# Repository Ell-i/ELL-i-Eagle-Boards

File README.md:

ELL-i Eagle Boards
==================

ELL-i Printed Circuit Boards in Eagle CAD format.

This repository contains both completed designs and designs that are
still work in progress.  The designs are licensed under Creative
Commons Attribution Share-Alike licence; for more information, see

  http://www.ell-i.org/Licensing

The designs (other than Ellduino) use components from the ELL-i and
SparkFun Eagle Libraries.  If you want to base your design on the
ELL-i designs, it is a good idea to install the ELL-i and SparkFun
Eagle Libraries; for more information, see

  https://github.com/Ell-i/ELL-i-Eagle-Libraries

Furthermore, you want to include the libraries into your library path,
as explained in README.md there.

Each of the directories in this repository forms a separate
(Eagle project)[https://learn.sparkfun.com/tutorials/using-eagle-schematic/create-a-project],
with its own (``eagle.epf`` file)[http://www.cadsoftusa.com/training/faq/#5].
The ``eagle.epf`` files stored in the repository have been carefully
hand-crafted, in order not to include any information about the active
windows, libraries, or the Eagle platform.

Modifying the project settings
------------------------------

By default, the Eagle projects in this repository have been stored
with auto-save off; that is, the ``eagle.epf`` file contains the
``AutoSaveProject=0`` directive.  Consequently, whenever you work on
the project, by default the window sizes and positions, etc, are not
saved.  If you *do* decide to save the settings (see below), you
*should* tell git to
(ignore local changes)[http://juststuffreally.blogspot.fi/2008/10/if-you-have-file-that-lives-in-git.html]
to ``eagle.epf``.

If you want to save the project settings, you can do that manually.
To do so, go to the *Control Panel* window in Eagle, and then select
``File->Save all`` from the menu.  This saves information about the
Eagle platform and Windows to the ``eagle.epf`` file.

After that, git will tell you that the ``eagle.epf`` file has been
changed and should be committed.  To tell git to ignore the local
changes, give the following command in the project directory:
```
git update-index --assume-unchanged build.properties
```
After that, git (ignores uncommitted
changes)[https://www.kernel.org/pub/software/scm/git/docs/git-update-index.html]
to the ``eagle.epf`` file.

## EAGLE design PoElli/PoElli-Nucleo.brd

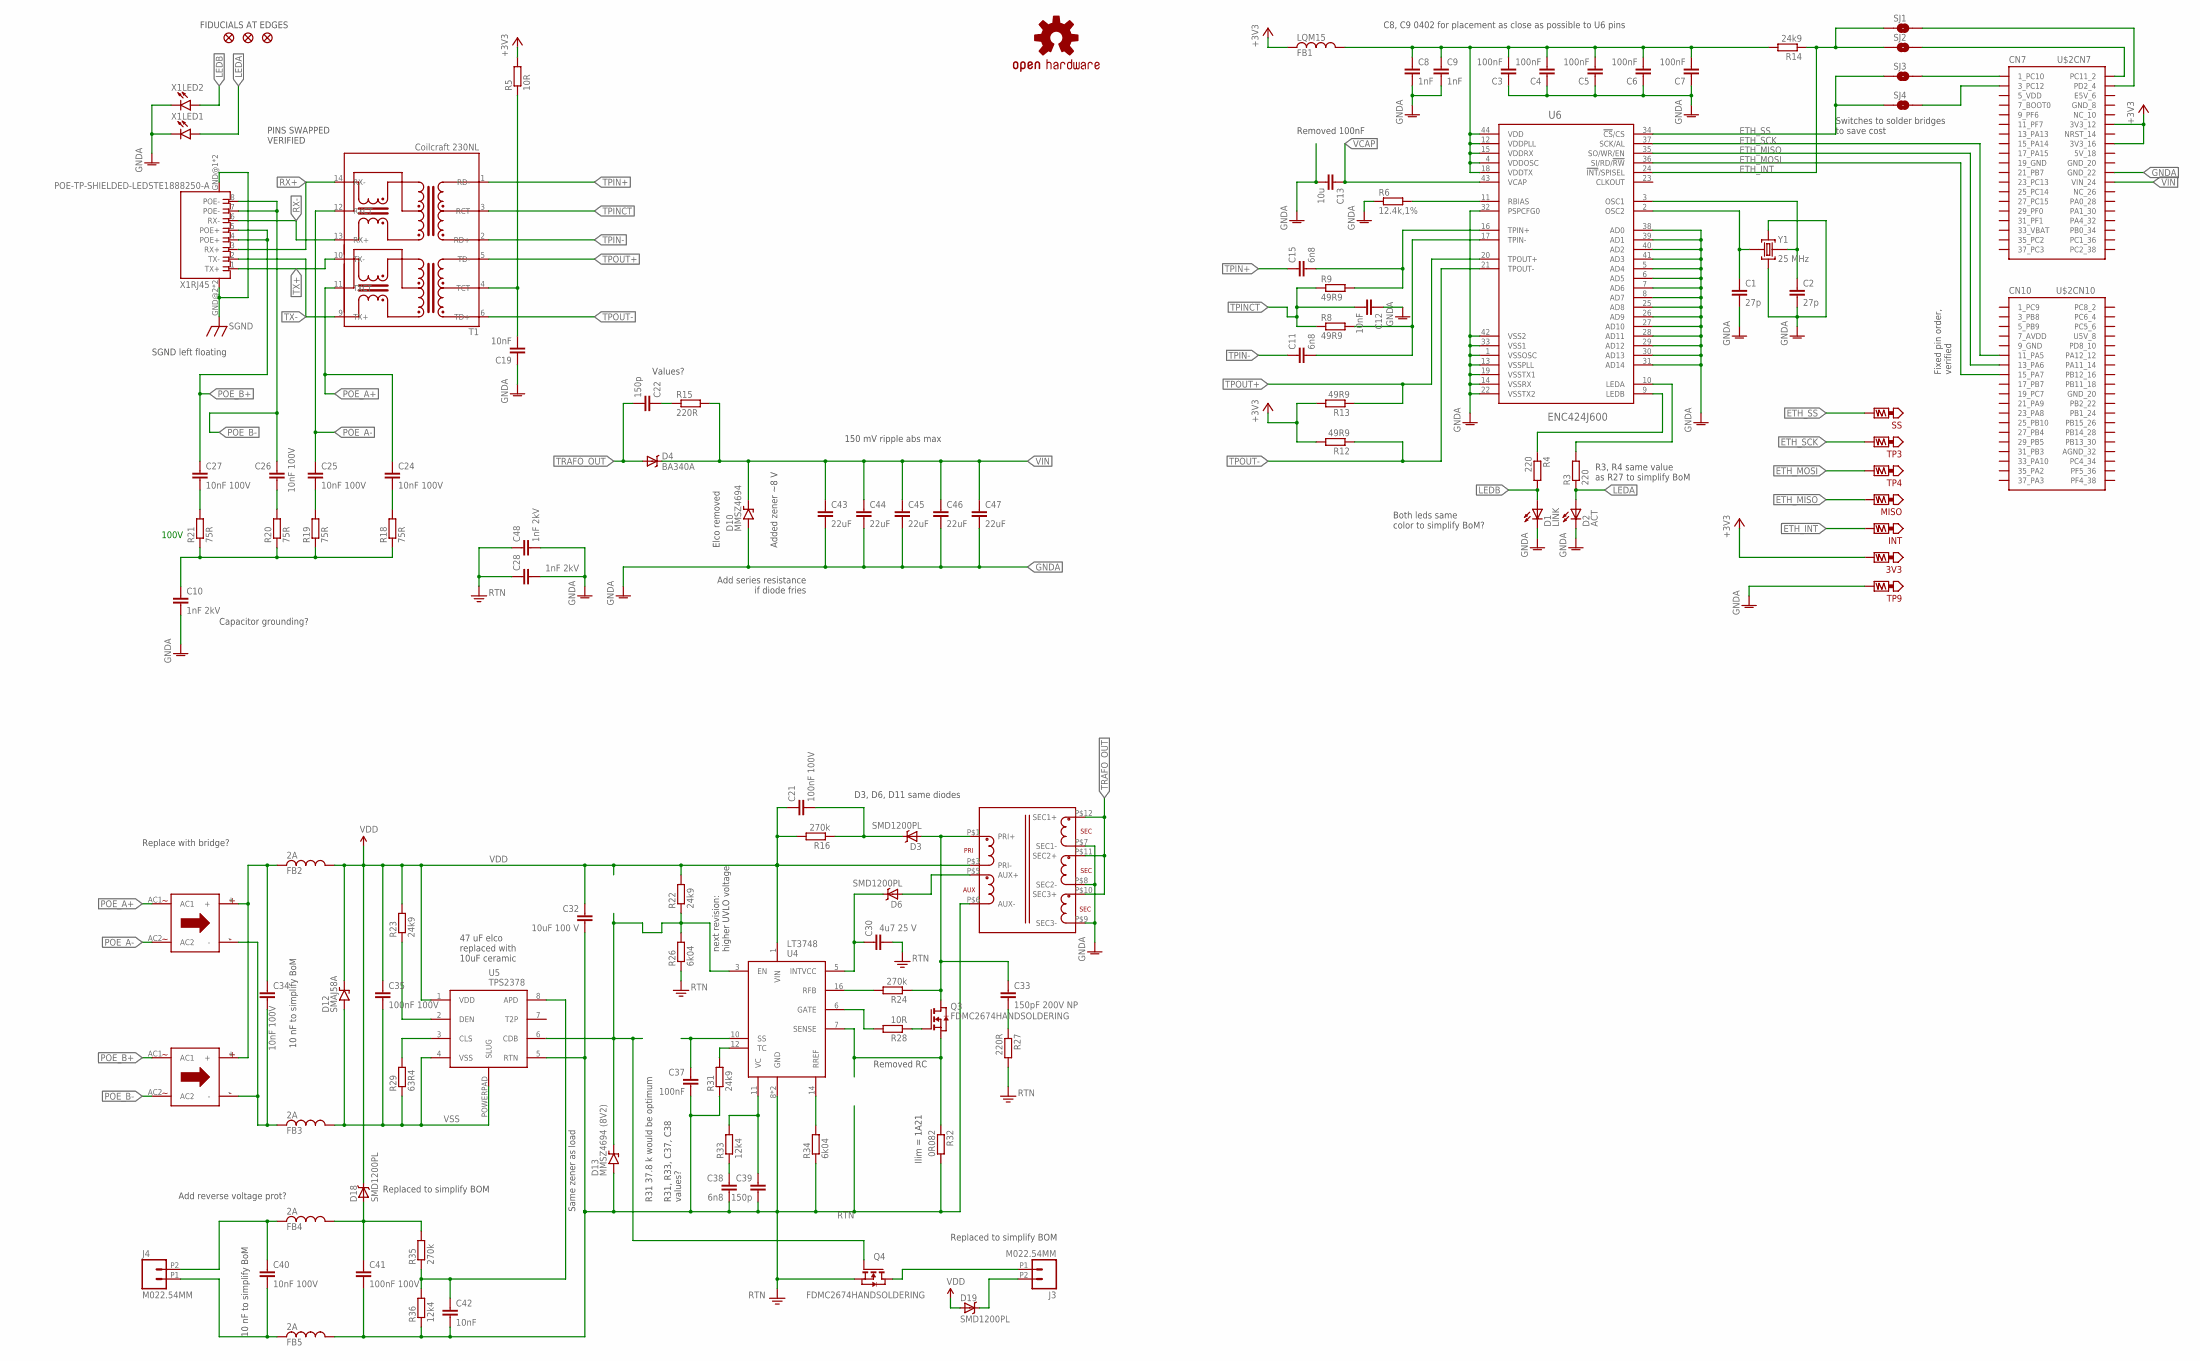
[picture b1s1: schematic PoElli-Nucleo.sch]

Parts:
3V3: 3V3; TP_5000
B1, B2: BRIDGE-RECTIFIER; MBS1
C1, C2: 27p; SMD0603-B
C3, C4, C5, C6, C7, C37: 100nF; SMD0603-B
C8, C9: 1nF; SMD0402-B
C10, C28, C48: 1nF 2kV; SMD1206-A
C11, C15, C38: 6n8; SMD0603-B
C12, C19, C42: 10nF; SMD0603-B
C13: 10u; SMD0603-B
C21, C35, C41: 100nF 100V; SMD0603-B
C22, C39: 150p; SMD0603-B
C24, C25, C26, C27, C34, C40: 10nF 100V; SMD0603-B
C30: 4u7 25 V; SMD0603-B
C32: 10uF 100 V; SMD2220-REFLOW
C33: 150pF 200V NP; SMD0603-B
C43, C44, C45, C46, C47: 22uF; SMD1206-A
D1: LINK; LED-0603
D2: ACT; LED-0603
D3, D6, D18, D19: SMD1200PL; SOD-123FL-A
D4: BA340A; SMA-DIODE
D10: MMSZ4694; SOD-123FL-A
D12: SMAJ58A; SMA
D13: MMSZ4694 (8V2); SOD-123FL-A
FB1: LQM15; SMD0603-A
FB2, FB3, FB4, FB5: 2A; SMD0603-A
FID1, FID2, FID3: FIDUCIAL1X2; FIDUCIAL-1X2
INT: TEST_POINT-5000; TP_5000
J3, J4: M022.54MM; 1X02_2.54_SCREWTERM
LOGO1: OSHW-LOGOM; OSHW-LOGO-M
MISO: MISO; TP_5021
Q3, Q4: FDMC2674HANDSOLDERING; MLP8L33_HS
R3, R4: 220; SMD0603-A
R5, R28: 10R; SMD0603-B
R6: 12.4k,1%; SMD0603-B
R8, R9, R12, R13: 49R9; SMD0603-B
R14: 24k9; SMD0603-A
R15, R27: 220R; SMD0603-B
R16: 270k; SMD0603-A
R18, R19, R20, R21: 75R; SMD0603-B
R22, R23, R31: 24k9; SMD0603-B
R24, R35: 270k; SMD0603-B
R26, R34: 6k04; SMD0603-B
R29: 63R4; SMD0603-B
R32: 0R082; SMD0603-B
R33, R36: 12k4; SMD0603-B
SJ1, SJ3: SOLDERJUMPERNC2; SJ_2S-NOTRACE
SJ2, SJ4: SOLDERJUMPERNO; SJ_2S-NO
SS: SS; TP_5021
T1: Coilcraft 230NL; COILCRAFT-ETH1-230L
T2: FLYBACK-3_OUTPUTS_749119350; WE_749119350
TP3: SCK; TP_5021
TP4: MOSI; TP_5021
TP9: GND; TP_5000
U4: LT3748; MSOP16(12)
U5: TPS2378; SO08-POWERPAD
U6: ENC424J600; TQFP44-0.8MM
U$2: NUCLEO-SHIELD-20PIN; NUCLEO-SHIELD-UNDERSIDE-SHORT-20-PINHEADER
X1: POE-TP-SHIELDED-LEDSTE1888250-A; TE1888250-A
Y1: 25 MHz; CRYSTAL-SMD-3225-GND

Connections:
+3V3: 3V3.P$1, FB1.P$1 (1), R5.P$2 (2), R12.P$2 (2), R13.P$2 (2), U$2.CN7_12 (3V3_12), U$2.CN7_16 (3V3_16)
ENC-3V3: C3.P$2 (2), C4.P$2 (2), C5.P$2 (2), C6.P$2 (2), C7.P$2 (2), C8.1, C9.1, FB1.P$2 (2), R14.P$2 (2), U6.4 (VDDOSC), U6.12 (VDDPLL), U6.15 (VDDRX), U6.18 (VDDTX), U6.44 (VDD)
ETH_INT: INT.P$1, R14.P$1 (1), SJ1.1, SJ2.1, U6.24 (!INT!/SPISEL)
ETH_MISO: MISO.P$1, U6.35 (SO/WR/EN), U$2.CN10_13 (13_PA6)
ETH_MOSI: TP4.P$1, U6.36 (SI/RD/!RW), U$2.CN10_15 (15_PA7)
ETH_SCK: TP3.P$1, U6.37 (SCK/AL), U$2.CN10_11 (11_PA5)
ETH_SS: SJ3.1, SJ4.1, SS.P$1, U6.34 (!CS!/CS)
GNDA: C1.P$2 (2), C2.P$2 (2), C3.P$1 (1), C4.P$1 (1), C5.P$1 (1), C6.P$1 (1), C7.P$1 (1), C8.2, C9.2, C10.P$2 (2), C12.P$1 (1), C13.P$2 (2), C19.P$1 (1), C28.P$2 (2), C43.P$2 (2), C44.P$2 (2), C45.P$2 (2), C46.P$2 (2), C47.P$2 (2), C48.P$2 (2), D1.C, D2.C, D10.A, R6.P$1 (1), T2.P$7 (SEC1-), T2.P$8 (SEC2-), T2.P$9 (SEC3-), TP9.P$1, U6.1 (VSSOSC), U6.5 (AD4), U6.6 (AD5), U6.7 (AD6), U6.8 (AD7), U6.13 (VSSPLL), U6.14 (VSSRX), U6.19 (VSSTX1), U6.22 (VSSTX2), U6.25 (AD8), U6.26 (AD9), U6.27 (AD10), U6.28 (AD11), U6.29 (AD12), U6.30 (AD13), U6.31 (AD14), U6.32 (PSPCFG0), U6.33 (VSS1), U6.38 (AD0), U6.39 (AD1), U6.40 (AD2), U6.41 (AD3), U6.42 (VSS2), U$2.CN7_22 (GND_22), X1.9 (C), X1.12 (C), Y1.2 (GND), Y1.4 (GND)
INTVCC: C30.P$1 (1), D6.C, U4.5 (INTVCC)
LEDA: D2.A, R3.P$1 (1), X1.10 (A)
LEDB: D1.A, R4.P$2 (2), X1.11 (A)
unnamed: J3.P1 (1), Q4.5 (D), Q4.6 (D), Q4.7 (D), Q4.8 (D), Q4.F1 (D)
unnamed: D19.C, J3.P2 (2)
unnamed: C10.P$1 (1), R18.P$1 (1), R19.P$1 (1), R20.P$1 (1), R21.P$1 (1)
unnamed: B1.+, B2.+, C34.P$1 (1), FB2.P$1 (1)
unnamed: R31.P$2 (2), U4.12 (TC)
unnamed: B1.-, B2.-, C34.P$2 (2), FB3.P$1 (1)
unnamed: SJ3.2, U$2.CN7_1 (1_PC10)
unnamed: SJ4.2, U$2.CN7_3 (3_PC12)
unnamed: SJ2.2, U$2.CN7_2 (PC11_2)
unnamed: SJ1.2, U$2.CN7_4 (PD2_4)
unnamed: C33.P$2 (2), R27.P$1 (1)
unnamed: C22.P$1 (1), R15.P$1 (1)
unnamed: R23.P$1 (1), U5.2 (DEN)
unnamed: R29.P$2 (2), U5.3 (CLS)
unnamed: C39.P$1 (1), R33.P$2 (2), U4.11 (VC)
unnamed: C38.P$1 (1), R33.P$1 (1)
unnamed: R28.P$2 (2), U4.6 (GATE)
unnamed: Q3.4 (G), R28.P$1 (1)
unnamed: Q3.1 (S), Q3.2 (S), Q3.3 (S), R32.P$1 (1), U4.7 (SENSE)
unnamed: C33.P$1 (1), D3.A, Q3.5 (D), Q3.6 (D), Q3.7 (D), Q3.8 (D), Q3.F1 (D), R24.P$1 (1), T2.P$1 (PRI+)
unnamed: D6.A, T2.P$5 (AUX+)
unnamed: R24.P$2 (2), U4.16 (RFB)
unnamed: R34.P$2 (2), U4.14 (RREF)
unnamed: C21.P$2 (2), D3.C, R16.P$1 (1)
unnamed: C1.P$1 (1), U6.2 (OSC2), Y1.1 (C1)
unnamed: C11.P$2 (2), R8.P$2 (2), U6.17 (TPIN-)
unnamed: C19.P$2 (2), R5.P$1 (1), T1.4 (TCT)
unnamed: R4.P$1 (1), U6.9 (LEDB)
unnamed: R3.P$2 (2), U6.10 (LEDA)
unnamed: R6.P$2 (2), U6.11 (RBIAS)
unnamed: C2.P$1 (1), U6.3 (OSC1), Y1.3 (C2)
unnamed: C27.P$2 (2), R21.P$2 (2)
unnamed: C24.P$2 (2), R18.P$2 (2)
unnamed: C25.P$2 (2), R19.P$2 (2)
unnamed: C26.P$2 (2), R20.P$2 (2)
unnamed: C40.P$1 (1), FB4.P$1 (1), J4.P2 (2)
unnamed: C42.P$1 (1), R35.P$1 (1), R36.P$2 (2), U5.8 (APD)
unnamed: C40.P$2 (2), FB5.P$1 (1), J4.P1 (1)
unnamed: C15.P$2 (2), R9.P$2 (2), U6.16 (TPIN+)
unnamed: C41.P$1 (1), D18.A, FB4.P$2 (2), R35.P$2 (2)
POE_A+: B1.AC1, C24.P$1 (1), T1.11 (TXCT)
POE_A-: B1.AC2, C25.P$1 (1), T1.12 (RXCT)
POE_B+: B2.AC1, C27.P$1 (1), X1.4 (POE+), X1.5 (POE+)
POE_B-: B2.AC2, C26.P$1 (1), X1.7 (POE-), X1.8 (POE-)
RTN: C28.P$1 (1), C30.P$2 (2), C32.P$2 (2), C37.P$2 (2), C38.P$2 (2), C39.P$2 (2), C41.P$2 (2), C42.P$2 (2), C48.P$1 (1), D13.A, FB5.P$2 (2), Q4.1 (S), Q4.2 (S), Q4.3 (S), R26.P$1 (1), R27.P$2 (2), R31.P$1 (1), R32.P$2 (2), R34.P$1 (1), R36.P$1 (1), T2.P$6 (AUX-), U4.8 (GND), U4.9 (GND), U5.5 (RTN)
RX+: T1.14 (RX-), X1.3 (RX+)
RX-: T1.13 (RX+), X1.6 (RX-)
SGND: X1.GND@1 (GND), X1.GND@2 (GND), X1.GND@3 (GND), X1.GND@4 (GND)
TPIN+: C15.P$1 (1), T1.1 (RD-)
TPIN-: C11.P$1 (1), T1.2 (RD+)
TPINCT: C12.P$2 (2), R8.P$1 (1), R9.P$1 (1), T1.3 (RCT)
TPOUT+: R13.P$1 (1), T1.5 (TD-), U6.20 (TPOUT+)
TPOUT-: R12.P$1 (1), T1.6 (TD+), U6.21 (TPOUT-)
TRAFO_OUT: C22.P$2 (2), D4.A, T2.P$10 (SEC3+), T2.P$11 (SEC2+), T2.P$12 (SEC1+)
TX+: T1.10 (TX-), X1.1 (TX+)
TX-: T1.9 (TX+), X1.2 (TX-)
U4_EN: D13.C, Q4.4 (G), R22.P$1 (1), R26.P$2 (2), U4.3 (EN), U5.6 (CDB)
U4_SS: C37.P$1 (1), U4.10 (SS)
VCAP: C13.P$1 (1), U6.43 (VCAP)
VDD: C21.P$1 (1), C32.P$1 (1), C35.P$1 (1), D12.C, D18.C, D19.A, FB2.P$2 (2), R16.P$2 (2), R22.P$2 (2), R23.P$2 (2), T2.P$3 (PRI-), U4.1 (VIN), U5.1 (VDD)
VIN: C43.P$1 (1), C44.P$1 (1), C45.P$1 (1), C46.P$1 (1), C47.P$1 (1), D4.C, D10.C, R15.P$2 (2), U$2.CN7_24 (VIN_24)
VSS: C35.P$2 (2), D12.A, FB3.P$2 (2), R29.P$1 (1), U5.4 (VSS), U5.POWERPAD (SLUG)

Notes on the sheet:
100V
Replace with bridge?
10 nF to simplify BoM
Add reverse voltage prot?
Both leds same color to simplify BoM?
R3, R4 same value as R27 to simplify BoM
R31, R33, C37, C38 values?
C8, C9 0402 for placement as close as possible to U6 pins
Values?
Removed 100nF
Switches to solder bridges to save cost
Elco removed
Added zener ~8 V
D3, D6, D11 same diodes
47 uF elco replaced with 10uF ceramic
Same zener as load
SGND left floating
150 mV ripple abs max
PINS SWAPPED VERIFIED
Capacitor grounding?
Removed RC
Ilim = 1A21
Fixed pin order, verified
Replaced to simplify BOM
FIDUCIALS AT EDGES
Add series resistance if diode fries
next revision: higher UVLO voltage
R31 37.8 k would be optimum

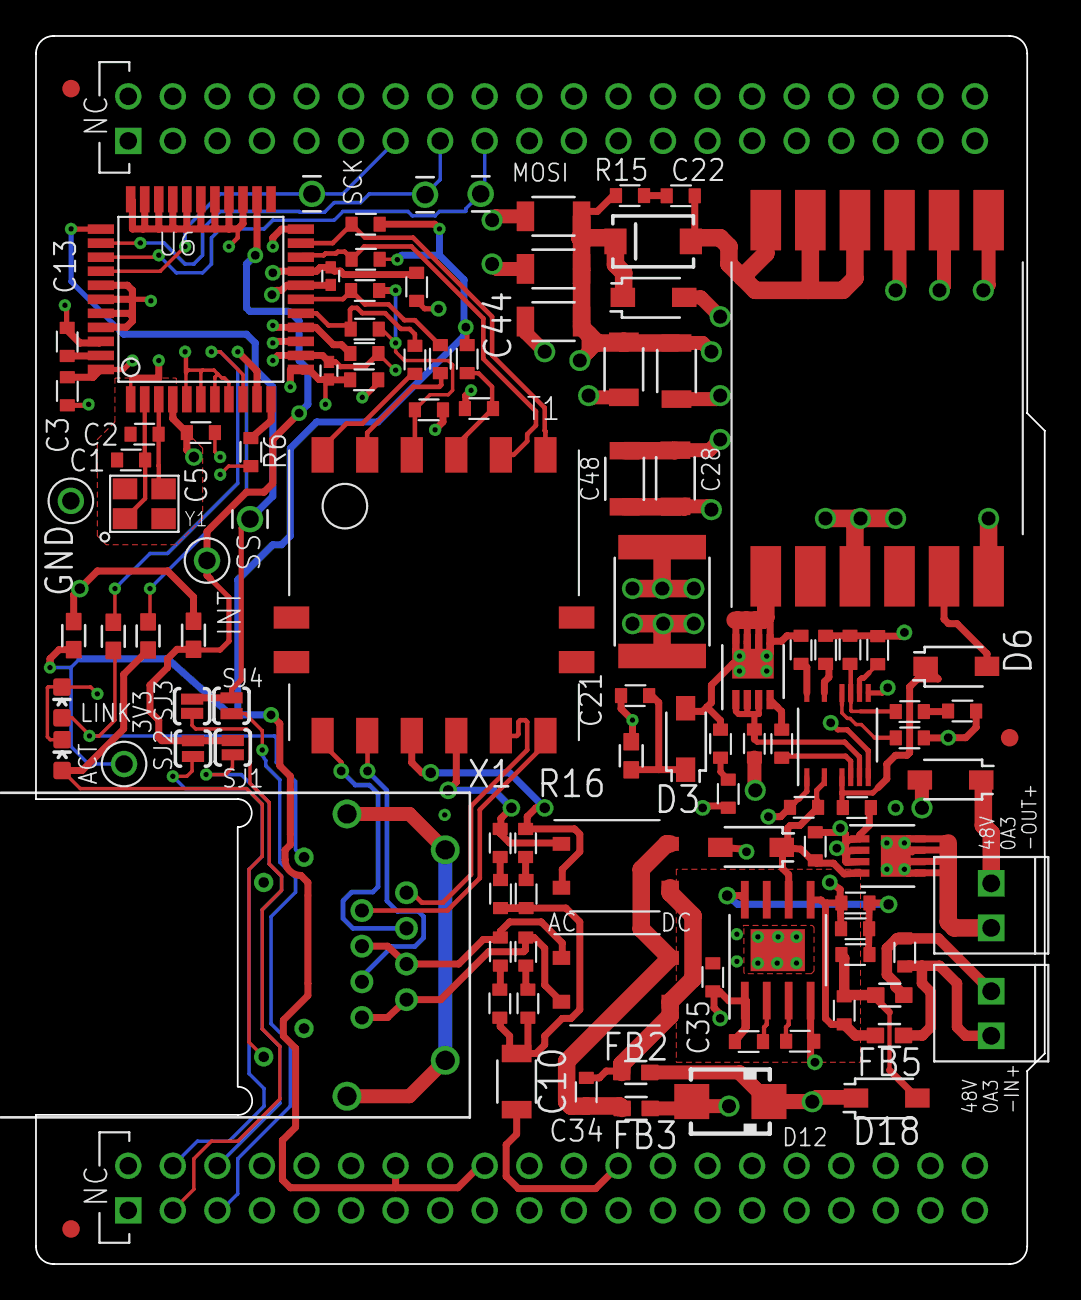
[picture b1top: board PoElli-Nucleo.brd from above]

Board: 4 copper layers, 57.5 x 70.0 mm, 111 parts (1 on the bottom side), 73 nets.

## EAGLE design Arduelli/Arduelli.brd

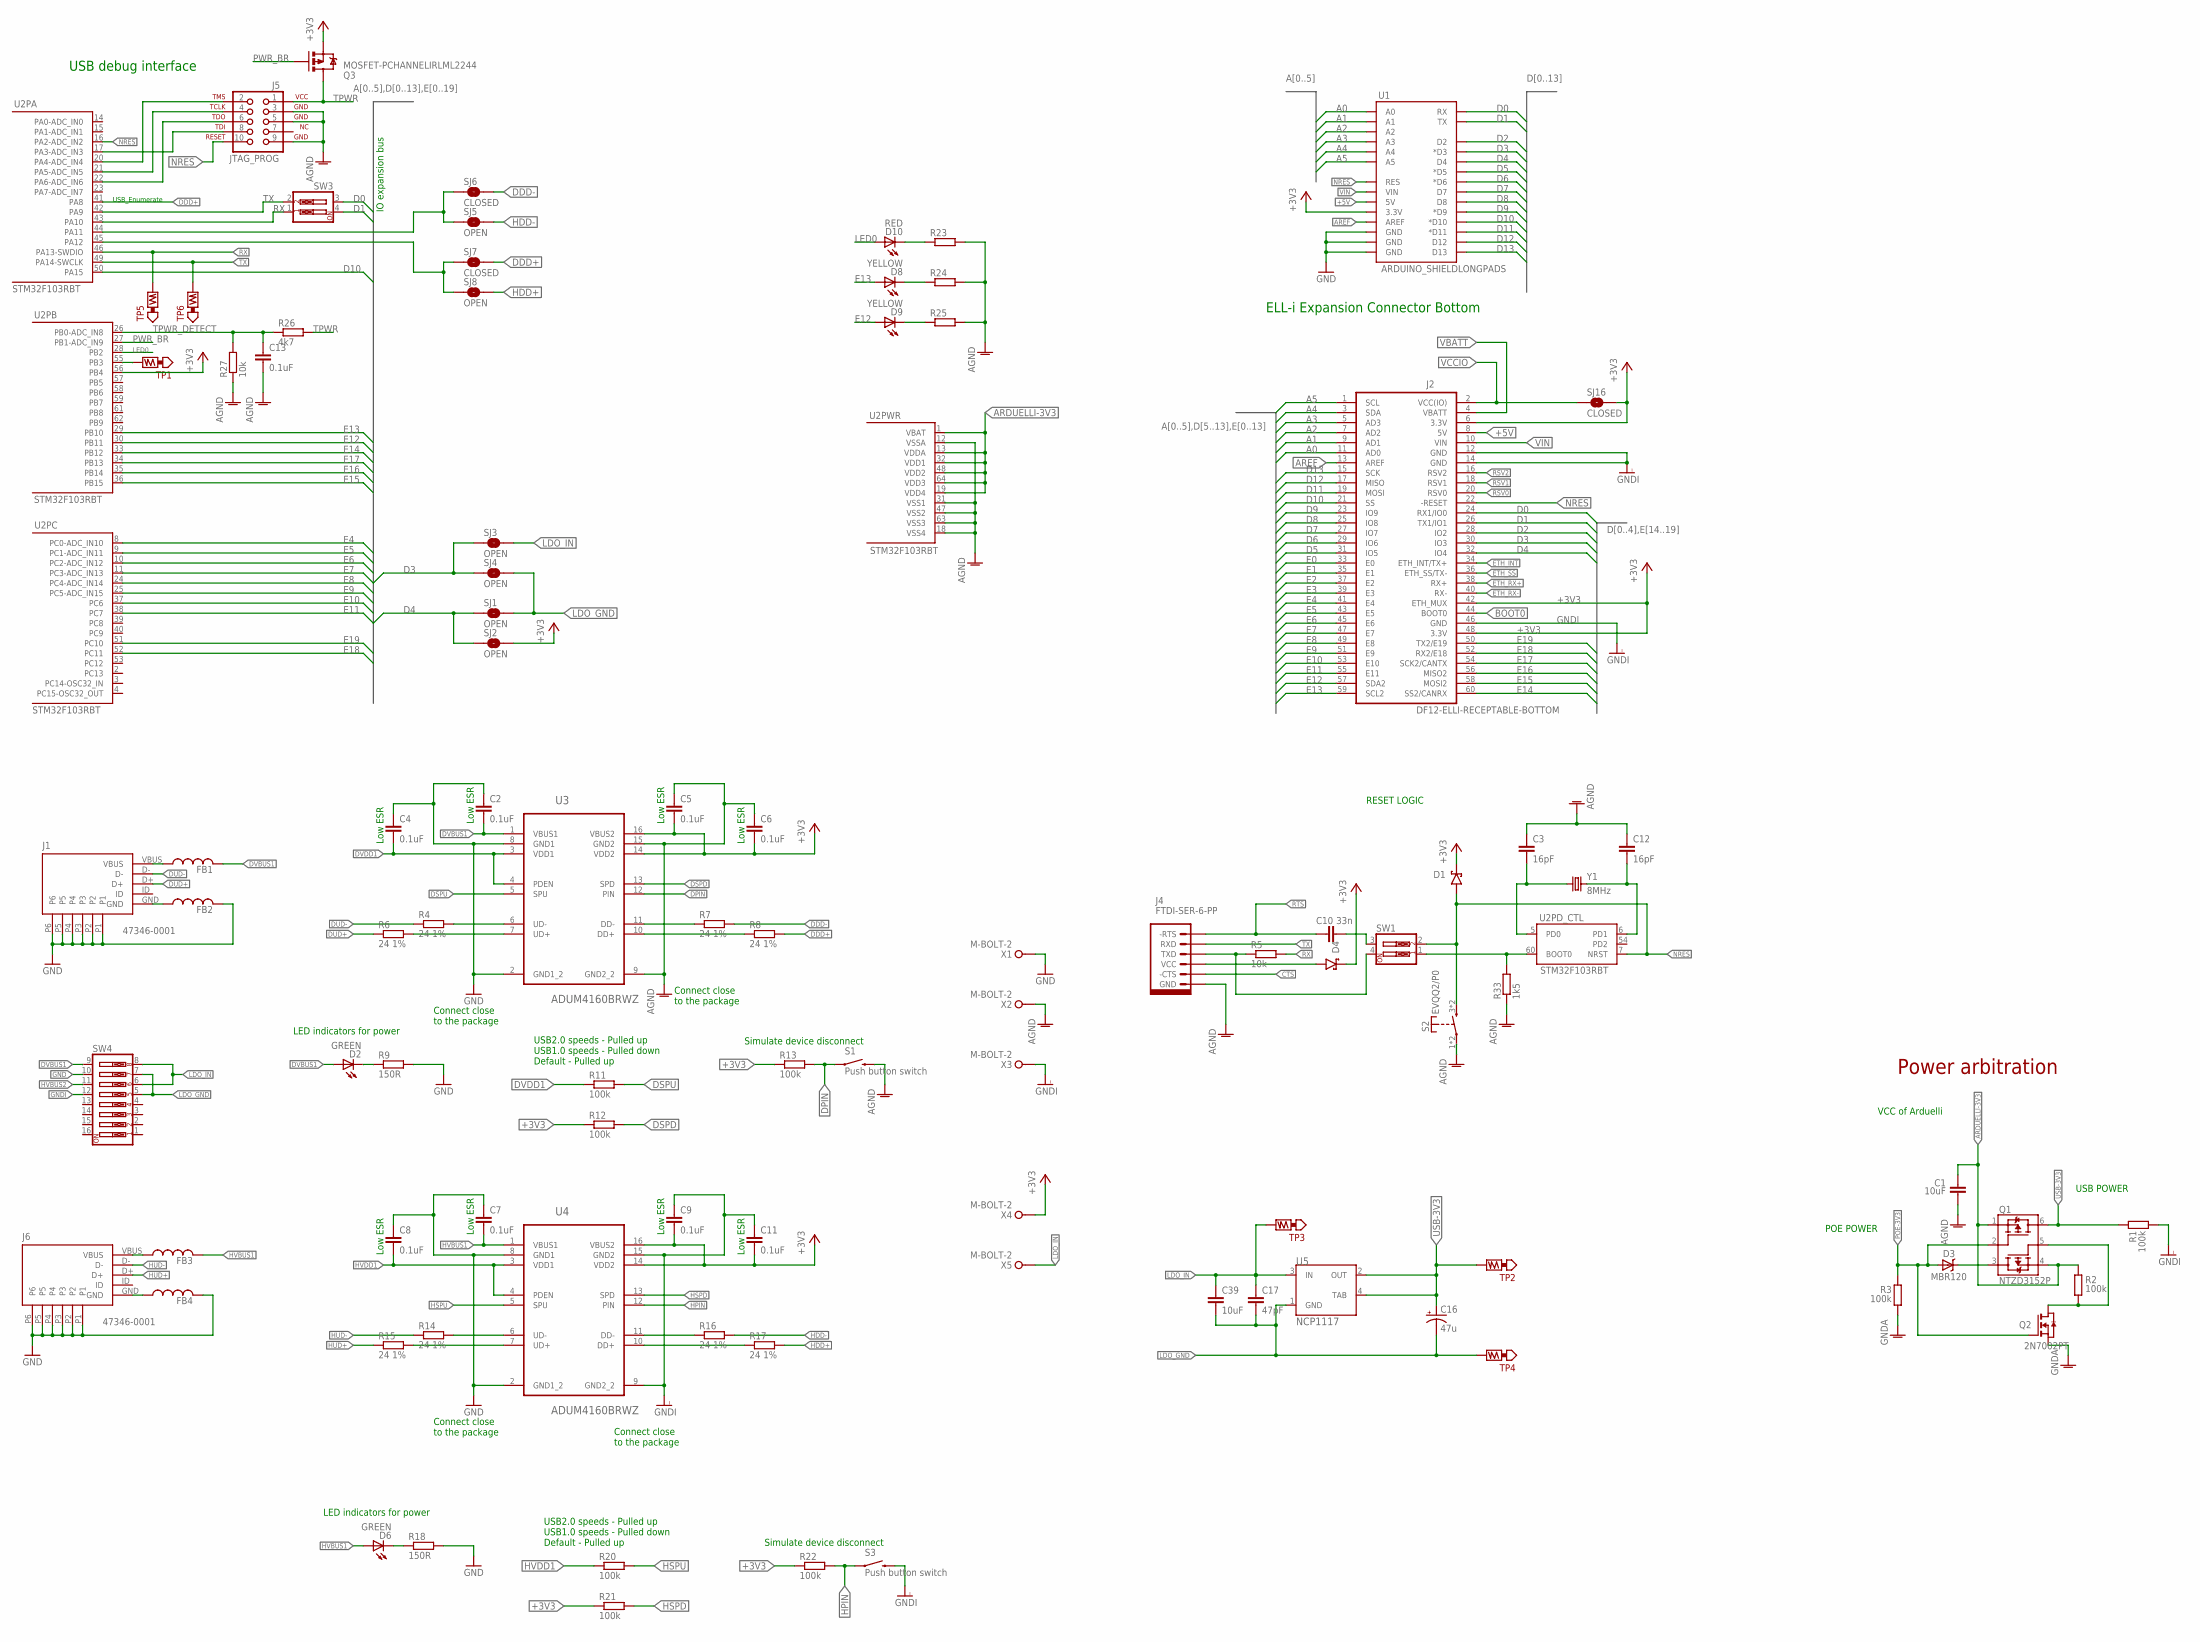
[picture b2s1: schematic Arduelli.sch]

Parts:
C1: 10uF; C0603
C2, C4, C5, C6, C7, C8, C9, C11, C13: 0.1uF; C0402
C3, C12: 16pF; C0402
C10: 33n; C0402
C16: 47u; CT6032
C17: 47pF; C0805
C39: 10uF; C0805
D1, D4: BAT60J; SOD323_DIODE
D2, D6: GREEN; LED-0603
D3: MBR120; DIODE-B2100
D8, D9: YELLOW; LED-0603
D10: RED; LED-0603
FB1, FB2, FB3, FB4: FB1206
J1, J6: 47346-0001; MICRO_USB
J2: DF12-ELLI-RECEPTABLE-BOTTOM; DF12-60DS-0.5V
J4: FTDI-SER-6-PP; FTDI-SER-6-SIL
J5: JTAG_PROG; CLP-105-02-X-D
Q1: NTZD3152P; SOT-563
Q2: 2N7002PT; SOT-416
Q3: MOSFET-PCHANNELIRLML2244; SOT23-3
R1, R2, R3, R11, R12, R13, R20, R21, R22: 100k; R0402
R4, R6, R7, R8, R14, R15, R16, R17: 24 1%; R0402
R5, R27: 10k; R0402
R9, R18: 150R; R0402
R23, R24, R25: R0402
R26: 4k7; R0402
R33: 1k5; R0402
S1, S3: Push button switch; TACTILE_SWITCH_SMD
S2: EVQQ2/P0
SJ1, SJ2, SJ3, SJ4, SJ5, SJ8: OPEN; SJ_2S-NO
SJ6, SJ7: CLOSED; SJ_2S-NO
SJ16: CLOSED; SJ_2S-TRACE
SW1, SW3: SW_DIP-2-SMT-HALFSIZE; DIPSWITCH-02-50MIL
SW4: SW_DIP-8-SMT-HALFSIZE; DIPSWITCH-08-50MIL
TP1, TP5, TP6: TEST_POINT-5000; TP_5021
TP2, TP3, TP4: TEST_POINT-5021; TP_5000
U1: ARDUINO_SHIELDLONGPADS; DUEMILANOVE_SHIELD_LONGPADS
U2: STM32F103RBT; LQFP64
U3, U4: ADUM4160BRWZ; SOIC127P1032X265-16N
U5: NCP1117; SOT223
X1, X2, X3, X4, X5: M-BOLT-2; M2-1
Y1: 8MHz; CRYSTAL-TXC-7A

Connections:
+3V3: C5.2, C6.2, C9.2, C11.2, D1.1 (C), D4.1 (C), J2.6 (3.3V), J2.42 (ETH_MUX), J2.48 (3.3V), Q3.2 (S), R12.1, R13.1, R21.1, R22.1, SJ2.2, SJ16.2, U1.3.3V, U2.56 (PB4), U3.14 (VDD2), U3.16 (VBUS2), U4.14 (VDD2), U4.16 (VBUS2), X4.1
+5V: J2.8 (5V), U1.5V
-RTS: C10.2, SW1.3
A0: J2.11 (AD0), U1.A0
A1: J2.9 (AD1), U1.A1
A2: J2.7 (AD2), U1.A2
A3: J2.5 (AD3), U1.A3
A4: J2.3 (SDA), U1.A4
A5: J2.1 (SCL), U1.A5
AGND: C1.2, C3.1, C5.1, C6.1, C12.1, C13.2, J4.GND, J5.3, J5.5, J5.9, R23.2, R24.2, R25.2, R27.1, R33.1, S1.3 (2), S2.1, S2.2, U2.12 (VSSA), U2.18 (VSS4), U2.31 (VSS1), U2.47 (VSS2), U2.63 (VSS3), U3.9 (GND2_2), U3.15 (GND2), X2.1
ARDUELLI-3V3: C1.1, Q1.1 (S1), Q1.4 (S2), R2.2, U2.1 (VBAT), U2.13 (VDDA), U2.19 (VDD4), U2.32 (VDD1), U2.48 (VDD2), U2.64 (VDD3)
AREF: J2.13 (AREF), U1.AREF
BOOT0: J2.44 (BOOT0), R33.2, SW1.1, U2.60 (BOOT0)
BOOT0TX: J4.TXD, R5.1, SW1.4
CTS: J4.-CTS
D0: J2.24 (RX1/IO0), SW3.3, U1.RX
D1: J2.26 (TX1/IO1), SW3.4, U1.TX
D2: J2.28 (IO2), U1.D2
D3: J2.30 (IO3), SJ3.1, SJ4.1, U1.D3 (*D3)
D4: J2.32 (IO4), SJ1.1, SJ2.1, U1.D4
D5: J2.31 (IO5), U1.D5 (*D5)
D6: J2.29 (IO6), U1.D6 (*D6)
D7: J2.27 (IO7), U1.D7
D8: J2.25 (IO8), U1.D8
D9: J2.23 (IO9), U1.D9 (*D9)
D10: J2.21 (SS), U1.D10 (*D10), U2.50 (PA15)
D11: J2.19 (MOSI), U1.D11 (*D11)
D12: J2.17 (MISO), U1.D12
D13: J2.15 (SCK), U1.D13
DDD+: R8.2, SJ7.1, SJ7.2, SJ8.1, U2.41 (PA8), U2.45 (PA12)
DDD-: R7.2, SJ5.1, SJ6.1, SJ6.2, U2.44 (PA11)
DPIN: R13.2, S1.1, U3.12 (PIN)
DSPD: R12.2, U3.13 (SPD)
DSPU: R11.2, U3.5 (SPU)
DUD+: J1.D+, R6.1
DUD-: J1.D-, R4.1
DVBUS1: C2.2, D2.A, FB1.1, SW4.9, U3.1 (VBUS1)
DVDD1: C4.2, R11.1, U3.3 (VDD1), U3.4 (PDEN)
E0: J2.33 (E0)
E1: J2.35 (E1)
E2: J2.37 (E2)
E3: J2.39 (E3)
E4: J2.41 (E4), U2.8 (PC0-ADC_IN10)
E5: J2.43 (E5), U2.9 (PC1-ADC_IN11)
E6: J2.45 (E6), U2.10 (PC2-ADC_IN12)
E7: J2.47 (E7), U2.11 (PC3-ADC_IN13)
E8: J2.49 (E8), U2.24 (PC4-ADC_IN14)
E9: J2.51 (E9), U2.25 (PC5-ADC_IN15)
E10: J2.53 (E10), U2.37 (PC6)
E11: J2.55 (E11), U2.38 (PC7)
E12: D9.A, J2.57 (SDA2), U2.30 (PB11)
E13: D8.A, J2.59 (SCL2), U2.29 (PB10)
E14: J2.60 (SS2/CANRX), U2.33 (PB12)
E15: J2.58 (MOSI2), U2.36 (PB15)
E16: J2.56 (MISO2), U2.35 (PB14)
E17: J2.54 (SCK2/CANTX), U2.34 (PB13)
E18: J2.52 (RX2/E18), U2.52 (PC11)
E19: J2.50 (TX2/E19), U2.51 (PC10)
ETH_INT: J2.34 (ETH_INT/TX+)
ETH_RX+: J2.38 (RX+)
ETH_RX-: J2.40 (RX-)
ETH_SS: J2.36 (ETH_SS/TX-)
GND: C2.1, C4.1, C7.1, C8.1, FB2.1, FB4.1, J1.P1, J1.P2, J1.P3, J1.P4, J1.P5, J1.P6, J6.P1, J6.P2, J6.P3, J6.P4, J6.P5, J6.P6, R9.2, R18.2, SW4.10, U1.GND@0 (GND), U1.GND@1 (GND), U1.GND@2 (GND), U3.2 (GND1_2), U3.8 (GND1), U4.2 (GND1_2), U4.8 (GND1), X1.1
GNDA: Q2.3 (S), R3.1
GNDI: C9.1, C11.1, J2.12 (GND), J2.14 (GND), J2.46 (GND), R1.1, S3.3 (2), SW4.12, U4.9 (GND2_2), U4.15 (GND2), X3.1
HDD+: R17.2, SJ8.2
HDD-: R16.2, SJ5.2
HPIN: R22.2, S3.1, U4.12 (PIN)
HSPD: R21.2, U4.13 (SPD)
HSPU: R20.2, U4.5 (SPU)
HUD+: J6.D+, R15.1
HUD-: J6.D-, R14.1
HVBUS1: C7.2, D6.A, FB3.1, U4.1 (VBUS1)
HVBUS2: SW4.11
HVDD1: C8.2, R20.1, U4.3 (VDD1), U4.4 (PDEN)
LDO_GND: C16.P$2 (-), C17.2, C39.2, SJ1.2, SJ4.2, SW4.5, SW4.7, TP4.P$1, U5.1 (GND)
LDO_IN: C17.1, C39.1, SJ3.2, SW4.6, SW4.8, TP3.P$1, U5.3 (IN), X5.1
LED0: D10.A, U2.28 (PB2)
unnamed: FB1.2, J1.VBUS
unnamed: D3.C, Q1.3 (D2)
unnamed: FB2.2, J1.GND
unnamed: D6.C, R18.1
unnamed: R4.2, U3.6 (UD-)
unnamed: R6.2, U3.7 (UD+)
unnamed: Q1.5 (G2), Q2.1 (D), R2.1
unnamed: C3.2, U2.5 (PD0), Y1.P$1 (1)
unnamed: C12.2, U2.6 (PD1), Y1.P$2 (2)
unnamed: D2.C, R9.1
unnamed: D10.C, R23.1
unnamed: D8.C, R24.1
unnamed: TP1.P$1, U2.55 (PB3)
unnamed: R7.1, U3.11 (DD-)
unnamed: R8.1, U3.10 (DD+)
unnamed: FB3.2, J6.VBUS
unnamed: FB4.2, J6.GND
unnamed: R14.2, U4.6 (UD-)
unnamed: R15.2, U4.7 (UD+)
unnamed: R16.1, U4.11 (DD-)
unnamed: R17.1, U4.10 (DD+)
unnamed: D9.C, R25.1
NRES: D1.2 (A), J2.22 (-RESET), J5.10, S2.3 (S), S2.4 (S), SW1.2, U1.RES, U2.7 (NRST), U2.16 (PA2-ADC_IN2)
POE-3V3: D3.A, Q1.2 (G1), Q2.2 (G), R3.2
PWR_BR: Q3.1 (G), U2.27 (PB1-ADC_IN9)
RSV0: J2.20 (RSV0)
RSV1: J2.18 (RSV1)
RSV2: J2.16 (RSV2)
RTS: C10.1, J4.-RTS
RX: R5.2, SW3.1, TP5.P$1, U2.43 (PA10), U2.46 (PA13-SWDIO)
TCLK: J5.4, U2.21 (PA5-ADC_IN5)
TDI: J5.8, U2.17 (PA3-ADC_IN3)
TDO: J5.6, U2.22 (PA6-ADC_IN6)
TMS: J5.2, U2.20 (PA4-ADC_IN4)
TPWR: J5.1, Q3.3 (D), R26.2
TPWR_DETECT: C13.1, R26.1, R27.2, U2.26 (PB0-ADC_IN8)
TX: J4.RXD, SW3.2, TP6.P$1, U2.42 (PA9), U2.49 (PA14-SWCLK)
USB-3V3: C16.P$1 (+), Q1.6 (D1), R1.2, TP2.P$1, U5.2 (OUT), U5.4 (TAB)
VBATT: J2.4 (VBATT)
VCC-IN: D4.2 (A), J4.VCC
VCCIO: J2.2 (VCC(IO)), SJ16.1
VIN: J2.10 (VIN), U1.VIN

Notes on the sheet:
Power arbitration
POE POWER
VCC of Arduelli
USB POWER
USB debug interface
IO expansion bus
RESET LOGIC
ELL-i Expansion Connector Bottom
USB2.0 speeds - Pulled up USB1.0 speeds - Pulled down Default - Pulled up
LED indicators for power
Simulate device disconnect
Connect close to the package
Low ESR
USB_Enumerate

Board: 2 copper layers, 94 parts (0 on the bottom side), 106 nets, no tracks yet.

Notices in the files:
parts and their libraries:
SparkFun-Boards: Licensing: CC v3.0 Share-Alike You are welcome to use this library for commercial purposes.
ELL-i-Passives: Eagle package Copyright (c) SparkFun under Creative Commons v3.0 Share Alike license.
